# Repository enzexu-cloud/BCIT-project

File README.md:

# 💫 About Me:
Enze Xu (徐恩泽) is a highly adaptable and analytical Mechatronics & Robotics student at BCIT specializing in automation control and embedded systems. After two years of intensive study, he has gained hands-on experience in PLC programming, circuit design, and microcontroller development, he has built a strong foundation in real-time control and system integration. Skilled in embedded C/ Assembly, hardware/software design, and diagnostics, he excels at developing and troubleshooting automation equipment.<br><br>He is passionate about contributing his expertise in automation and embedded technology.

## 🌐 Socials:

# 💻 Tech Stack:
      
# 📊 GitHub Stats:
<br/>
<br/>

---

<!-- Proudly created with GPRM ( https://gprm.itsvg.in ) -->

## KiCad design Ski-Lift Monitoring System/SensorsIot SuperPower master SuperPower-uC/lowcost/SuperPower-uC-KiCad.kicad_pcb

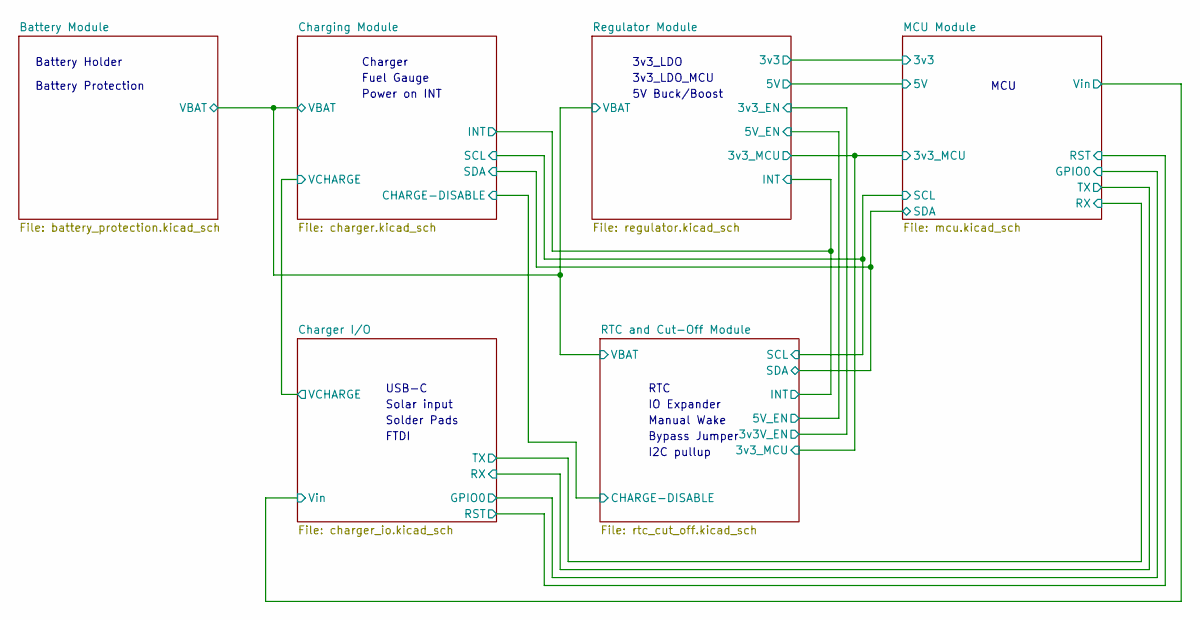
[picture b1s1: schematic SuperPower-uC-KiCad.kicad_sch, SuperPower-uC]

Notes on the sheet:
Battery Protection
Solar input
Bypass Jumper
3v3_LDO
3v3_LDO_MCU
RTC
Battery Holder
I2C pullup
5V Buck/Boost
MCU
FTDI
Fuel Gauge
Charger
Power on INT
IO Expander
USB-C
Manual Wake
Solder Pads

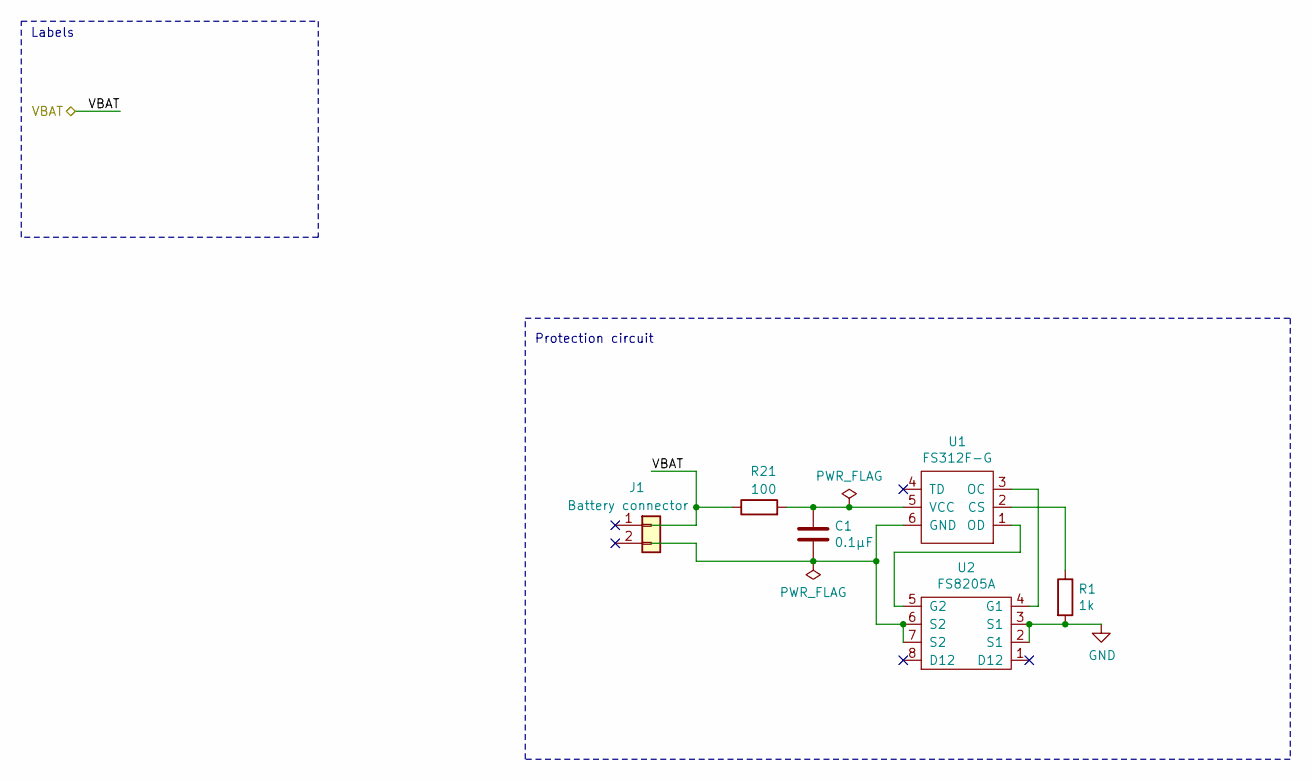
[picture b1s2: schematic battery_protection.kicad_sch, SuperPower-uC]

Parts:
C1: 0.1µF; C_0603_1608Metric_Pad1.08x0.95mm_HandSolder; LCSC C14858
J1: Battery connector; JST_EH_S2B-EH_1x02_P2.50mm_Horizontal; LCSC C157931
R1: 1k; R_0603_1608Metric_Pad0.98x0.95mm_HandSolder; LCSC C21190
R21: 100; R_0603_1608Metric_Pad0.98x0.95mm_HandSolder; LCSC C22775
U1: FS312F-G; SOT-23-6_Handsoldering; LCSC C82736
U2: FS8205A; TSSOP-8_4.4x3mm_P0.65mm; LCSC C16052

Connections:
/Battery Module/VBAT: J1.1, R21.1; also elsewhere on the board
GND: R1.2, U2.2 (S1), U2.3 (S1); also elsewhere on the board
unnamed: C1.1, R21.2, U1.5 (VCC)
unnamed: R1.1, U1.2 (CS)
unnamed: U1.1 (OD), U2.5 (G2)
unnamed: U1.3 (OC), U2.4 (G1)

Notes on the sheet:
Protection circuit
Labels

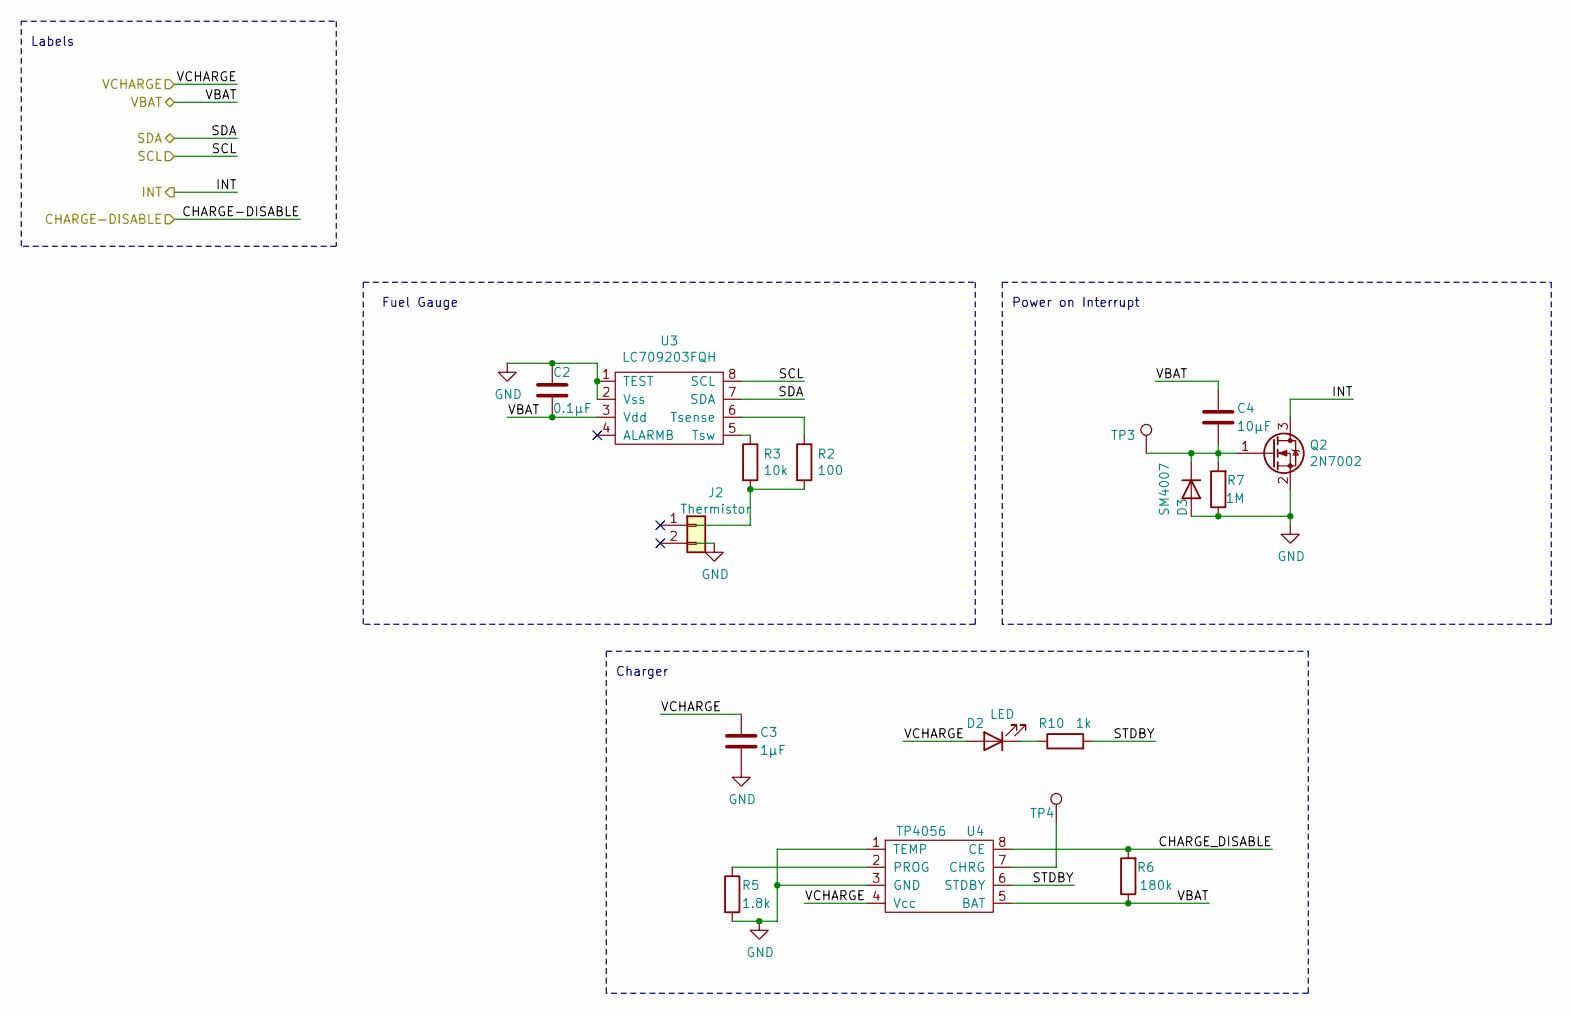
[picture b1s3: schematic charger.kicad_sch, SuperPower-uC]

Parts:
C2: 0.1µF; C_0603_1608Metric_Pad1.08x0.95mm_HandSolder; LCSC C14858
C3: 1µF; C_0603_1608Metric_Pad1.08x0.95mm_HandSolder; LCSC C15849
C4: 10µF; C_0603_1608Metric_Pad1.08x0.95mm_HandSolder; LCSC C19702
D2: LED; LED_0603_1608Metric_Pad1.05x0.95mm_HandSolder; LCSC C72041
D3: SM4007; D_MELF; LCSC C64898
J2: Thermistor; JST_EH_S2B-EH_1x02_P2.50mm_Horizontal; LCSC C76589
Q2: 2N7002; SOT-23; LCSC C8545
R2: 100; R_0603_1608Metric_Pad0.98x0.95mm_HandSolder; LCSC C22775
R3: 10k; R_0603_1608Metric_Pad0.98x0.95mm_HandSolder; LCSC C25804
R5: 1.8k; R_0603_1608Metric_Pad0.98x0.95mm_HandSolder; LCSC C4177
R6: 180k; R_0603_1608Metric_Pad0.98x0.95mm_HandSolder; LCSC C22827
R7: 1M; R_0603_1608Metric_Pad0.98x0.95mm_HandSolder; LCSC C22935
R10: 1k; R_0603_1608Metric_Pad0.98x0.95mm_HandSolder; LCSC C21190
TP3, TP4: TestPoint; TestPoint_Pad_1.5x1.5mm
U3: LC709203FQH; WDFN-8-1EP_4x3mm_P0.65mm_EP2.4x1.8mm; LCSC C152311
U4: TP4056; SOP-8_3.9x4.9mm_P1.27mm; LCSC C16581

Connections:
/Battery Module/VBAT: C2.2, C4.1, R6.1, U3.3 (Vdd), U4.5 (BAT); also elsewhere on the board
/Charger I/O/VCHARGE: C3.1, D2.2 (A), U4.4 (Vcc); also elsewhere on the board
/Charging Module/INT: Q2.3 (D); also elsewhere on the board
/Charging Module/SCL: U3.8 (SCL); also elsewhere on the board
/Charging Module/SDA: U3.7 (SDA); also elsewhere on the board
/Charging Module/STDBY: R10.2, U4.6 (STDBY)
CH_DIS: R6.2, U4.8 (CE); also elsewhere on the board
GND: C2.1, C3.2, D3.2 (A), J2.2, Q2.2 (S), R5.2, R7.1, U3.1 (TEST), U3.2 (Vss), U4.1 (TEMP), U4.3 (GND); also elsewhere on the board
unnamed: C4.2, D3.1 (K), Q2.1 (G), R7.2, TP3.1
unnamed: D2.1 (K), R10.1
unnamed: R2.1, U3.6 (Tsense)
unnamed: R3.1, U3.5 (Tsw)
unnamed: R5.1, U4.2 (PROG)
unnamed: TP4.1, U4.7 (CHRG)

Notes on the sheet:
Labels
Charger
Power on Interrupt
Fuel Gauge

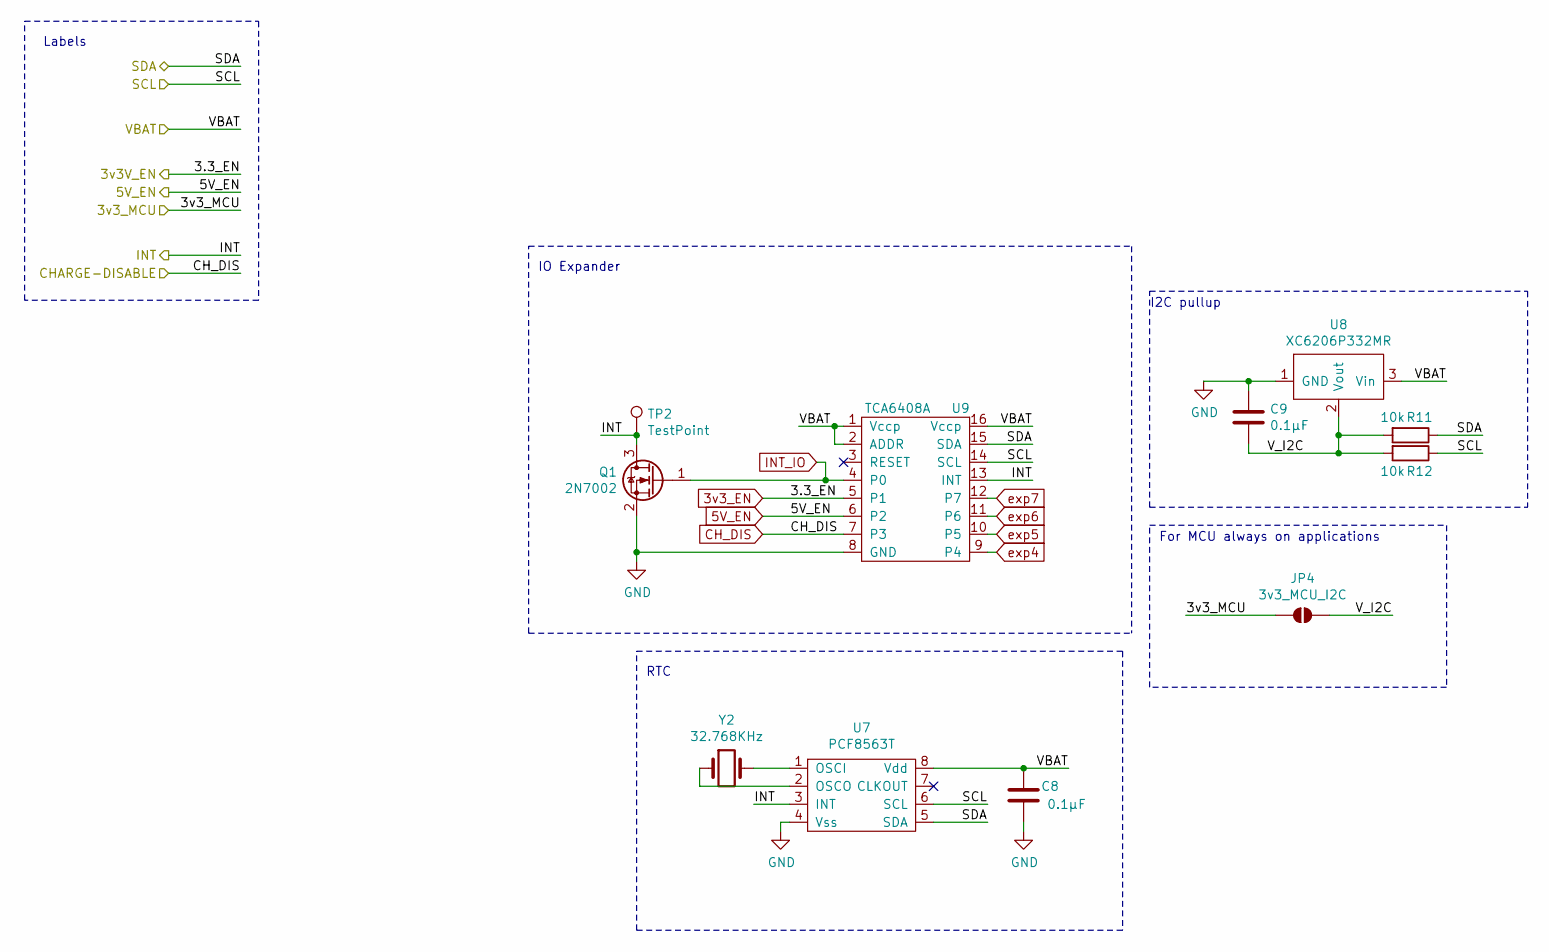
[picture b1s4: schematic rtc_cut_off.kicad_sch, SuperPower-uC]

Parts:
C8, C9: 0.1µF; C_0603_1608Metric_Pad1.08x0.95mm_HandSolder; LCSC C14858
JP4: 3v3_MCU_I2C; SolderJumper-2_P1.3mm_Open_Pad1.0x1.5mm
Q1: 2N7002; SOT-23; LCSC C8545
R11, R12: 10k; R_0603_1608Metric_Pad0.98x0.95mm_HandSolder; LCSC C25804
TP2: TestPoint; TestPoint_Pad_1.5x1.5mm
U7: PCF8563T; SOIC-8_3.9x4.9mm_P1.27mm; LCSC C7440
U8: XC6206P332MR; SOT-23_Handsoldering; LCSC C5446
U9: TCA6408A; TSSOP-16_4.4x5mm_P0.65mm; LCSC C206177
Y2: 32.768KHz; Crystal_SMD_3215-2Pin_3.2x1.5mm; LCSC C32346

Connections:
3v3_EN: U9.5 (P1); also elsewhere on the board
5V_EN: U9.6 (P2); also elsewhere on the board
/Battery Module/VBAT: C8.2, U7.8 (Vdd), U8.3 (Vin), U9.1 (Vccp), U9.2 (ADDR), U9.16 (Vccp); also elsewhere on the board
/Charging Module/INT: Q1.3 (D), TP2.1, U7.3 (INT), U9.13 (INT); also elsewhere on the board
/Charging Module/SCL: R12.1, U7.6 (SCL), U9.14 (SCL); also elsewhere on the board
/Charging Module/SDA: R11.1, U7.5 (SDA), U9.15 (SDA); also elsewhere on the board
/MCU Module/3v3_MCU: JP4.1 (A); also elsewhere on the board
/RTC and Cut-Off Module/V_I2C: C9.2, JP4.2 (B), R11.2, R12.2, U8.2 (Vout)
CH_DIS: U9.7 (P3); also elsewhere on the board
GND: C8.1, C9.1, Q1.2 (S), U7.4 (Vss), U8.1 (GND), U9.8 (GND); also elsewhere on the board
INT_IO: Q1.1 (G), U9.4 (P0); also elsewhere on the board
unnamed: U7.1 (OSCI), Y2.2
unnamed: U7.2 (OSCO), Y2.1
exp4: U9.9 (P4); also elsewhere on the board
exp5: U9.10 (P5); also elsewhere on the board
exp6: U9.11 (P6); also elsewhere on the board
exp7: U9.12 (P7); also elsewhere on the board

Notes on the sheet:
For MCU always on applications
I2C pullup
Labels
IO Expander
RTC

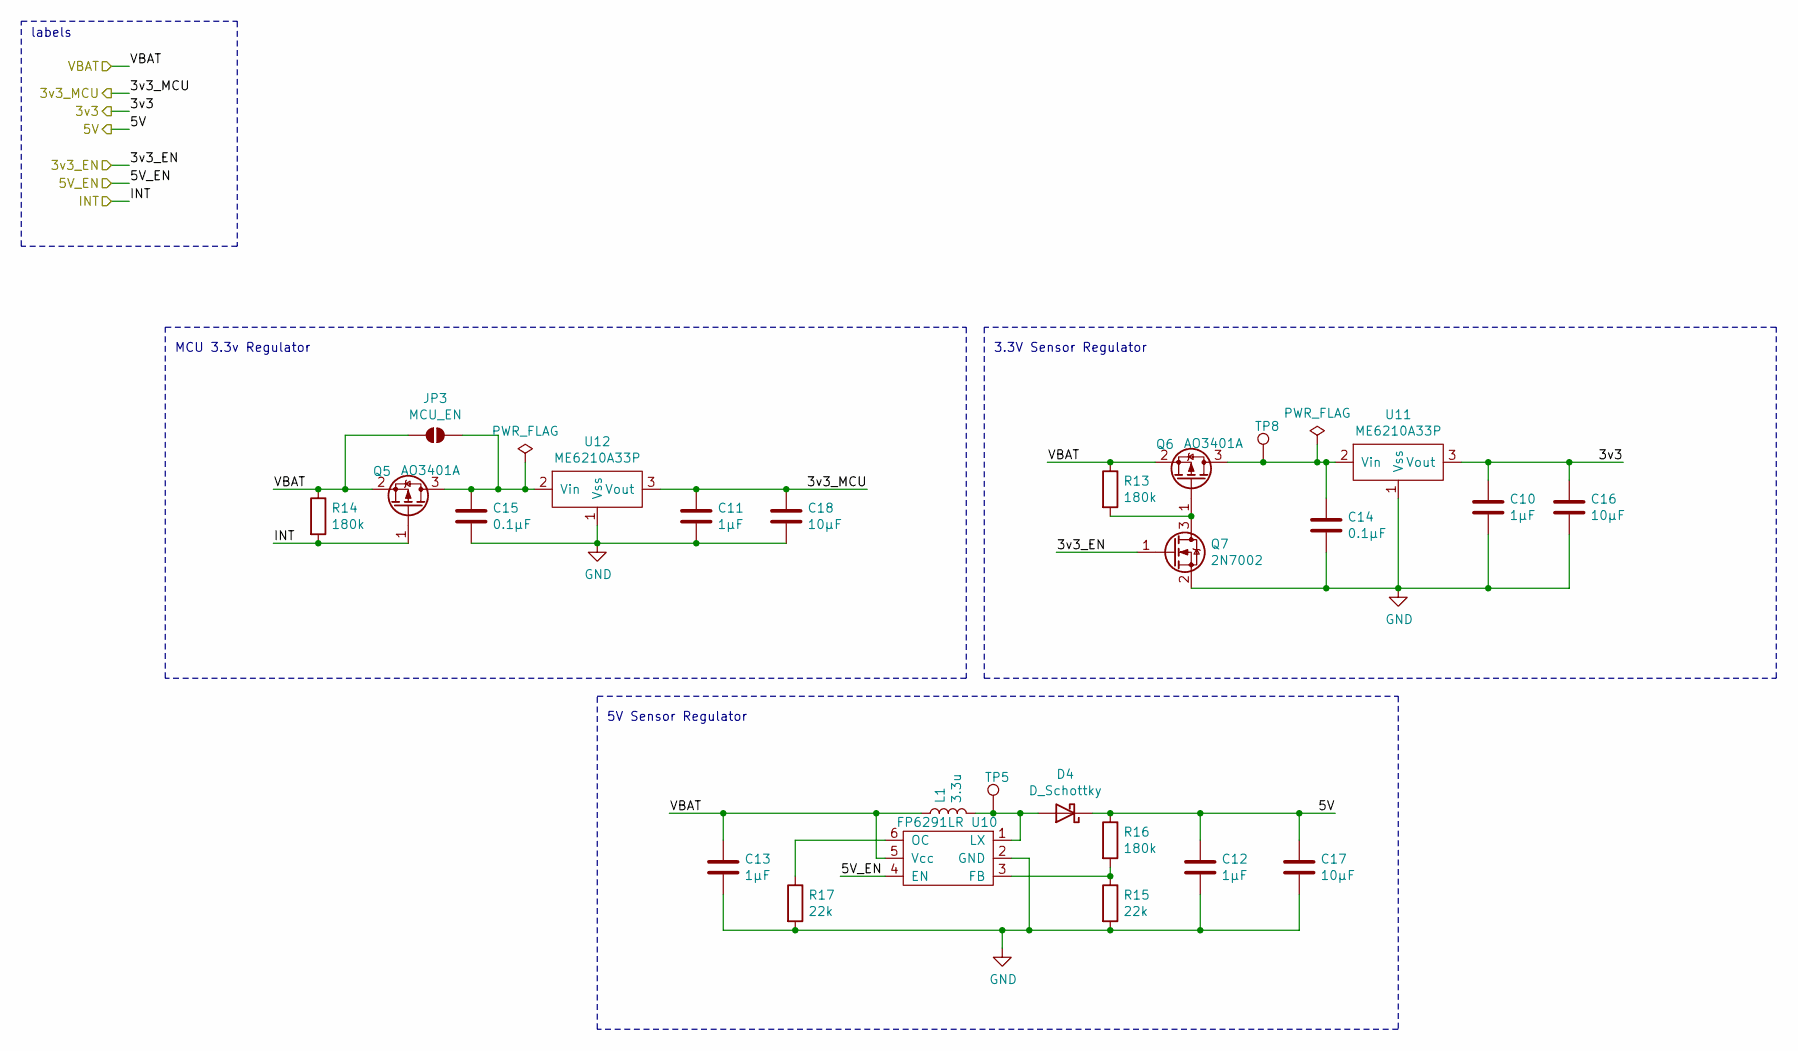
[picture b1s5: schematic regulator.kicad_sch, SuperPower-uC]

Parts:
C10, C11, C12, C13: 1µF; C_0603_1608Metric_Pad1.08x0.95mm_HandSolder; LCSC C15849
C14, C15: 0.1µF; C_0603_1608Metric_Pad1.08x0.95mm_HandSolder; LCSC C14858
C16, C17, C18: 10µF; C_0603_1608Metric_Pad1.08x0.95mm_HandSolder; LCSC C19702
D4: D_Schottky; D_SOD-123; LCSC C8598
JP3: MCU_EN; SolderJumper-2_P1.3mm_Open_Pad1.0x1.5mm
L1: 3.3u; L_Bourns_SRP7028A_7.3x6.6mm; LCSC C280586
Q5, Q6: AO3401A; SOT-23_Handsoldering; LCSC C347476
Q7: 2N7002; SOT-23; LCSC C8545
R13, R14, R16: 180k; R_0603_1608Metric_Pad0.98x0.95mm_HandSolder; LCSC C22827
R15, R17: 22k; R_0603_1608Metric_Pad0.98x0.95mm_HandSolder; LCSC C17560
TP5, TP8: TestPoint; TestPoint_Pad_1.5x1.5mm
U10: FP6291LR; SOT-23-6_Handsoldering; LCSC C18701
U11, U12: ME6210A33P; SOT-89-3_Handsoldering; LCSC C85233

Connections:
3v3_EN: Q7.1 (G); also elsewhere on the board
5V_EN: U10.4 (EN); also elsewhere on the board
/Battery Module/VBAT: C13.1, JP3.1 (A), L1.1, Q5.2 (S), Q6.2 (S), R13.1, R14.1, U10.5 (Vcc); also elsewhere on the board
/Charging Module/INT: Q5.1 (G), R14.2; also elsewhere on the board
/MCU Module/3v3: C10.1, C16.1, U11.3 (Vout); also elsewhere on the board
/MCU Module/3v3_MCU: C11.1, C18.1, U12.3 (Vout); also elsewhere on the board
/MCU Module/5V: C12.1, C17.1, D4.1 (K), R16.1; also elsewhere on the board
GND: C10.2, C11.2, C12.2, C13.2, C14.2, C15.2, C16.2, C17.2, C18.2, Q7.2 (S), R15.2, R17.2, U10.2 (GND), U11.1 (Vss), U12.1 (Vss); also elsewhere on the board
unnamed: C14.1, Q6.3 (D), TP8.1, U11.2 (Vin)
unnamed: C15.1, JP3.2 (B), Q5.3 (D), U12.2 (Vin)
unnamed: D4.2 (A), L1.2, TP5.1, U10.1 (LX)
unnamed: Q6.1 (G), Q7.3 (D), R13.2
unnamed: R15.1, R16.2, U10.3 (FB)
unnamed: R17.1, U10.6 (OC)

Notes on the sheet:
MCU 3.3v Regulator
3.3V Sensor Regulator
labels
5V Sensor Regulator

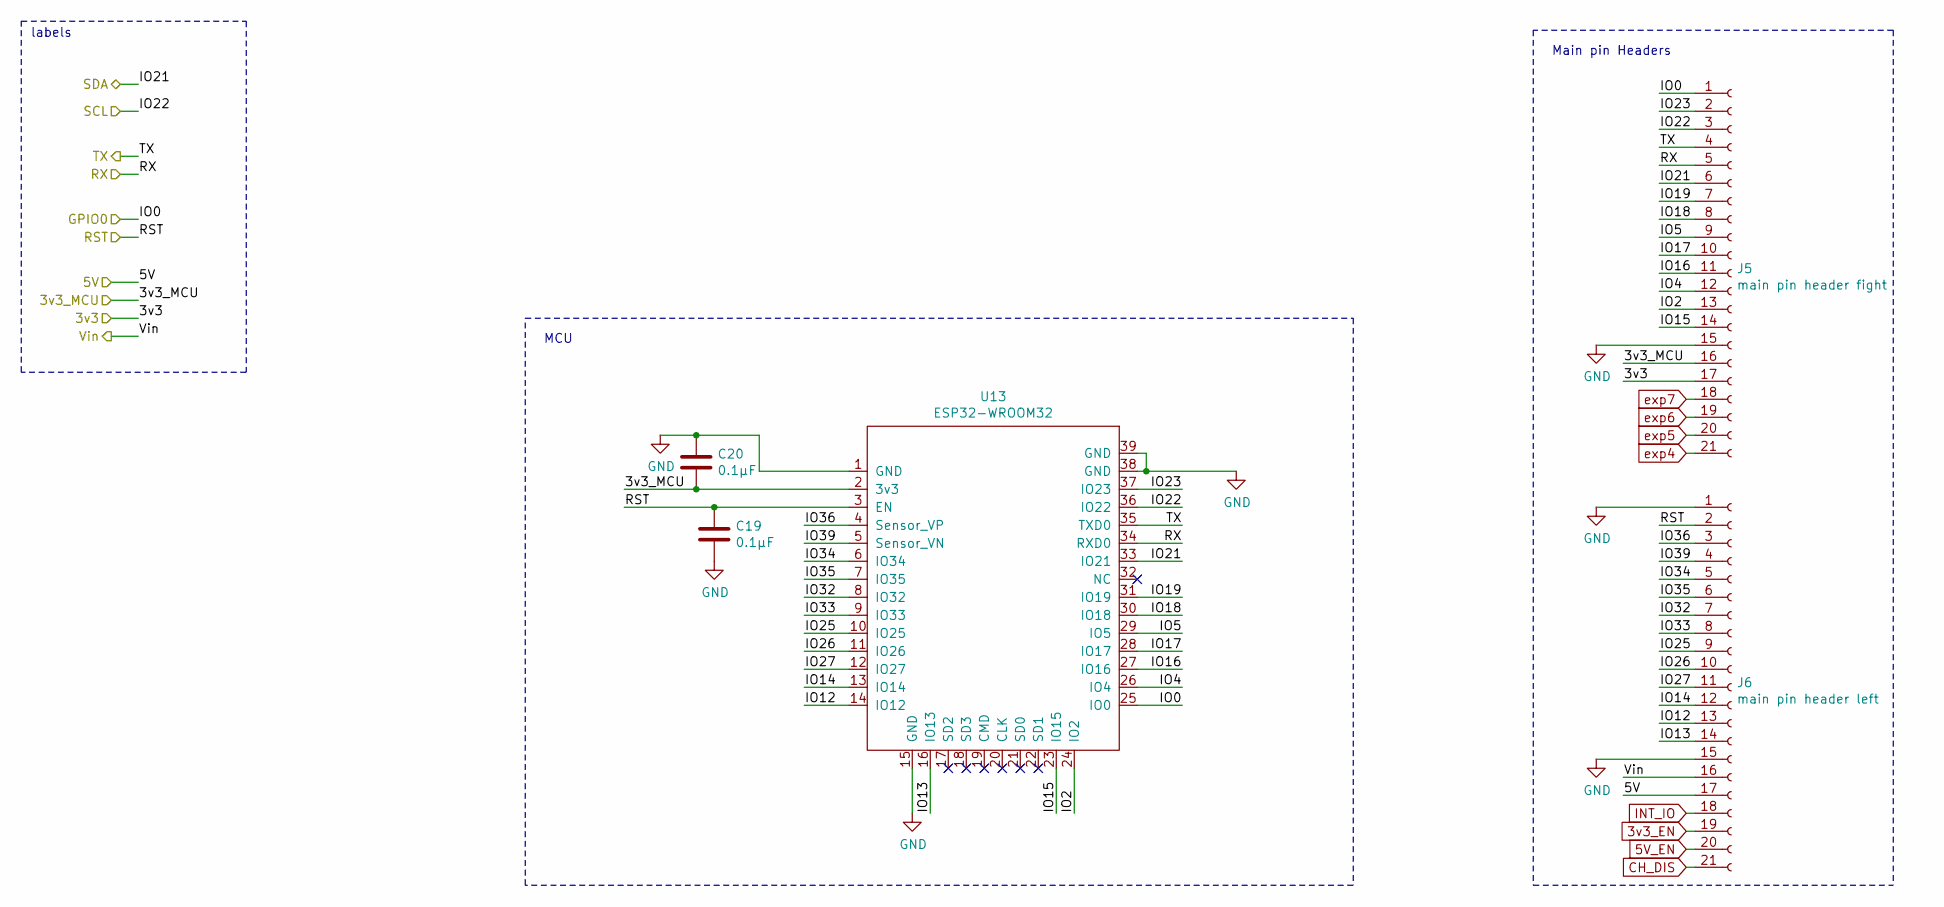
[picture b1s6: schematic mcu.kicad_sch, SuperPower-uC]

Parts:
C19, C20: 0.1µF; C_0603_1608Metric_Pad1.08x0.95mm_HandSolder; LCSC C14858
J5: main pin header fight; PinSocket_1x21_P2.54mm_Vertical
J6: main pin header left; PinSocket_1x21_P2.54mm_Vertical
U13: ESP32-WROOM32; ESP32-WROOM-32; LCSC C82899

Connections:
3v3_EN: J6.19; also elsewhere on the board
5V_EN: J6.20; also elsewhere on the board
/Charger I/O/GPIO0: J5.1, U13.25 (IO0); also elsewhere on the board
/Charger I/O/RST: C19.1, J6.2, U13.3 (EN); also elsewhere on the board
/Charger I/O/RX: J5.4, U13.35 (TXD0); also elsewhere on the board
/Charger I/O/VCHARGE: J6.16; also elsewhere on the board
/Charging Module/SCL: J5.3, U13.36 (IO22); also elsewhere on the board
/Charging Module/SDA: J5.6, U13.33 (IO21); also elsewhere on the board
/MCU Module/3v3: J5.17; also elsewhere on the board
/MCU Module/3v3_MCU: C20.2, J5.16, U13.2 (3v3); also elsewhere on the board
/MCU Module/5V: J6.17; also elsewhere on the board
/MCU Module/IO2: J5.13, U13.24 (IO2)
/MCU Module/IO4: J5.12, U13.26 (IO4)
/MCU Module/IO5: J5.9, U13.29 (IO5)
/MCU Module/IO12: J6.13, U13.14 (IO12)
/MCU Module/IO13: J6.14, U13.16 (IO13)
/MCU Module/IO14: J6.12, U13.13 (IO14)
/MCU Module/IO15: J5.14, U13.23 (IO15)
/MCU Module/IO16: J5.11, U13.27 (IO16)
/MCU Module/IO17: J5.10, U13.28 (IO17)
/MCU Module/IO18: J5.8, U13.30 (IO18)
/MCU Module/IO19: J5.7, U13.31 (IO19)
/MCU Module/IO23: J5.2, U13.37 (IO23)
/MCU Module/IO25: J6.9, U13.10 (IO25)
/MCU Module/IO26: J6.10, U13.11 (IO26)
/MCU Module/IO27: J6.11, U13.12 (IO27)
/MCU Module/IO32: J6.7, U13.8 (IO32)
/MCU Module/IO33: J6.8, U13.9 (IO33)
/MCU Module/IO34: J6.5, U13.6 (IO34)
/MCU Module/IO35: J6.6, U13.7 (IO35)
/MCU Module/IO36: J6.3, U13.4 (Sensor_VP)
/MCU Module/IO39: J6.4, U13.5 (Sensor_VN)
/MCU Module/RX: J5.5, U13.34 (RXD0); also elsewhere on the board
CH_DIS: J6.21; also elsewhere on the board
GND: C19.2, C20.1, J5.15, J6.1, J6.15, U13.1 (GND), U13.15 (GND), U13.38 (GND), U13.39 (GND); also elsewhere on the board
INT_IO: J6.18; also elsewhere on the board
exp4: J5.21; also elsewhere on the board
exp5: J5.20; also elsewhere on the board
exp6: J5.19; also elsewhere on the board
exp7: J5.18; also elsewhere on the board

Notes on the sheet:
labels
MCU
Main pin Headers

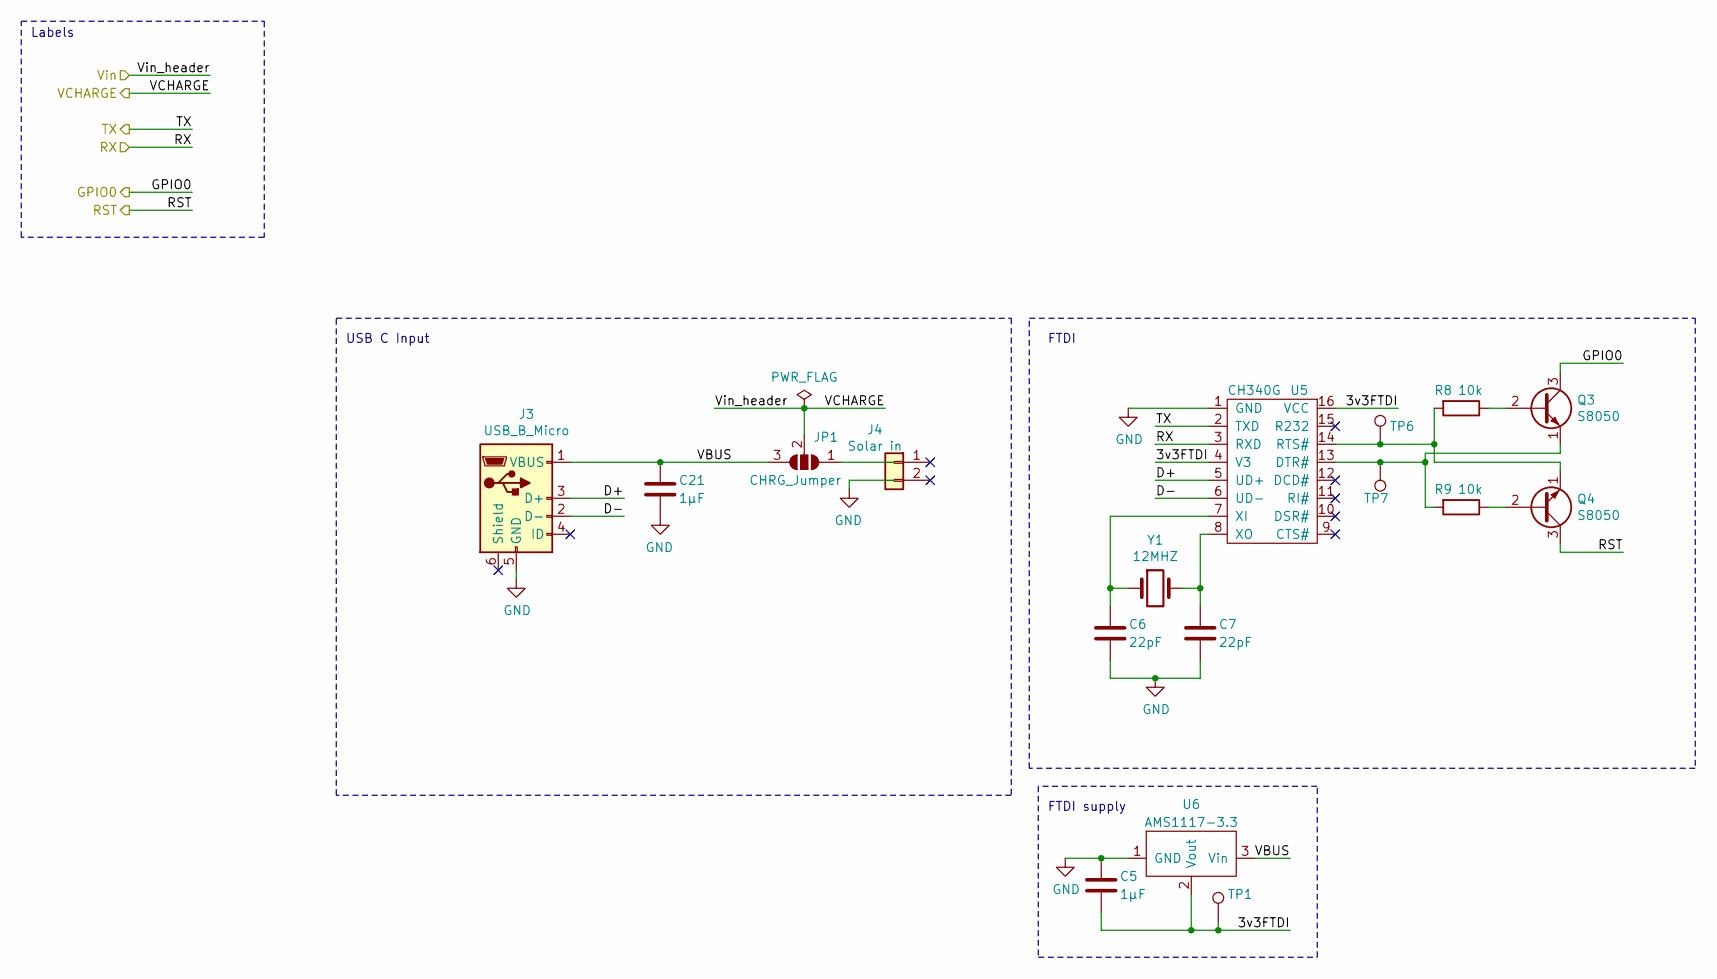
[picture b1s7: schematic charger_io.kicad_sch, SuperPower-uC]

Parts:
C5, C21: 1µF; C_0603_1608Metric_Pad1.08x0.95mm_HandSolder; LCSC C15849
C6: 22pF; R_0603_1608Metric_Pad0.98x0.95mm_HandSolder; LCSC C1653
C7: 22pF; C_0603_1608Metric_Pad1.08x0.95mm_HandSolder; LCSC C1653
J3: USB_B_Micro; USB_Micro-B_Molex-105017-0001; LCSC C319164
J4: Solar in; JST_EH_S2B-EH_1x02_P2.50mm_Horizontal; LCSC C157931
JP1: CHRG_Jumper; SolderJumper-3_P1.3mm_Open_Pad1.0x1.5mm
Q3, Q4: S8050; SOT-23_Handsoldering; LCSC C111272
R8, R9: 10k; R_0603_1608Metric_Pad0.98x0.95mm_HandSolder; LCSC C25804
TP1, TP6, TP7: TestPoint; TestPoint_Pad_1.5x1.5mm
U5: CH340G; SOP-16_4.55x10.3mm_P1.27mm; LCSC C14267
U6: AMS1117-3.3; SOT-223-3_TabPin2; LCSC C6186
Y1: 12MHZ; Crystal_SMD_3225-4Pin_3.2x2.5mm_HandSoldering; LCSC C9002

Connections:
/Charger I/O/3v3FTDI: C5.2, TP1.1, U5.4 (V3), U5.16 (VCC), U6.2 (Vout)
/Charger I/O/D+: J3.3 (D+), U5.5 (UD+)
/Charger I/O/D-: J3.2 (D-), U5.6 (UD-)
/Charger I/O/GPIO0: Q3.3 (C); also elsewhere on the board
/Charger I/O/RST: Q4.3 (C); also elsewhere on the board
/Charger I/O/RX: U5.3 (RXD); also elsewhere on the board
/Charger I/O/VBUS: C21.1, J3.1 (VBUS), JP1.3 (B), U6.3 (Vin)
/Charger I/O/VCHARGE: JP1.2 (C); also elsewhere on the board
/MCU Module/RX: U5.2 (TXD); also elsewhere on the board
GND: C5.1, C6.2, C7.2, C21.2, J3.5 (GND), J4.2, U5.1 (GND), U6.1 (GND); also elsewhere on the board
unnamed: C6.1, U5.7 (XI), Y1.1
unnamed: C7.1, U5.8 (XO), Y1.2
unnamed: J4.1, JP1.1 (A)
unnamed: Q3.1 (E), R9.2, TP7.1, U5.13 (DTR#)
unnamed: Q3.2 (B), R8.1
unnamed: Q4.1 (E), R8.2, TP6.1, U5.14 (RTS#)
unnamed: Q4.2 (B), R9.1

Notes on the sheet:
FTDI supply
USB C Input
Labels
FTDI

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
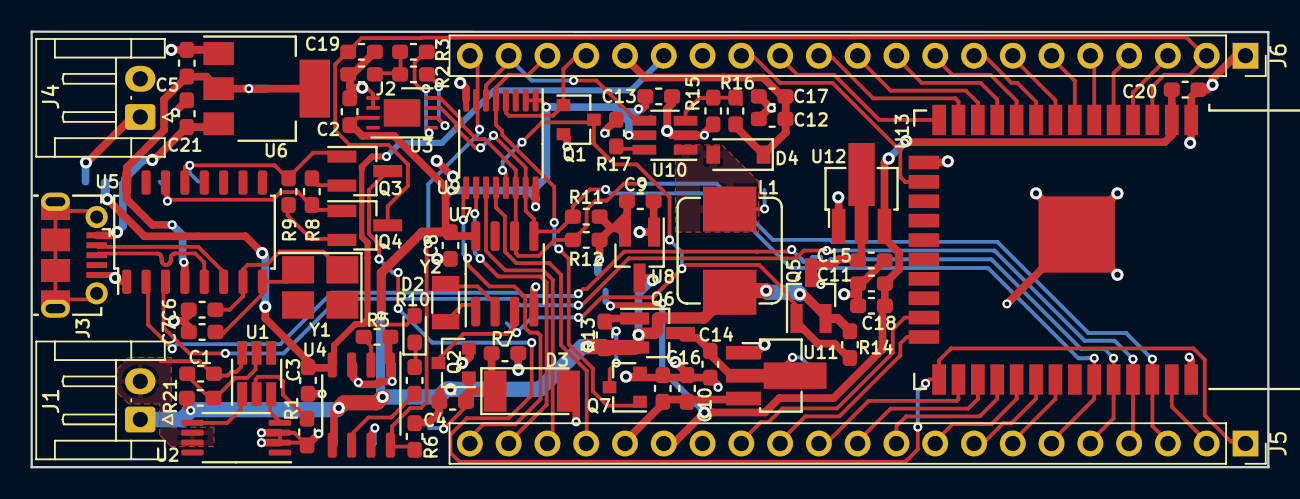
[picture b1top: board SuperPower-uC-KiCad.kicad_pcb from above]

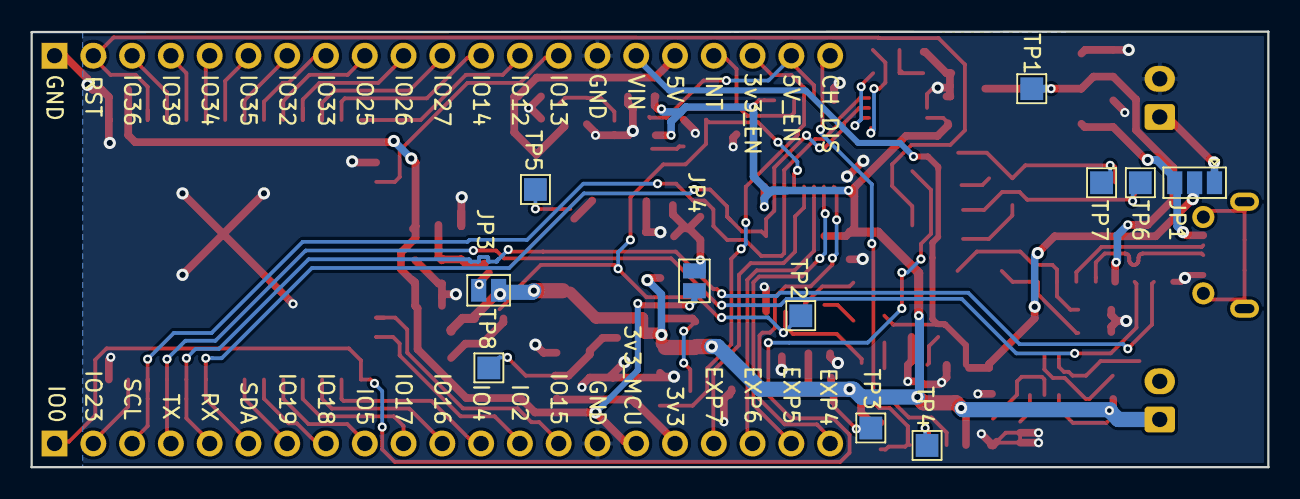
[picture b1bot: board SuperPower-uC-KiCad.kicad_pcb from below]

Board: 2 copper layers, 81.0 x 28.5 mm, 81 parts (11 on the bottom side), 75 nets.

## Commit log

2025-01-16 Create MSP430 PWM Control Code
2025-01-16 Create MSP430 Software Encoder Code
2025-01-16 Create MSP430 Keypad PWM Control Code
2025-01-20 Upload electrical labs
2025-01-20 Upload MSP430 projects from ROBT 3356 Controller System
2025-01-21 Updated folder name
2025-01-21 Created images folder
2025-05-19 Upload Ski-Lift project
2025-05-19 Upload PCB design
2025-05-19 Upload SuperPower BOM
2025-05-19 Upload project budget plan
2025-05-19 Upload poster
2025-05-21 Upload PLC Elevator Project
2025-05-21 Upload pdf report

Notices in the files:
Ski-Lift Monitoring System/SensorsIot SuperPower master SuperPower-uC/lowcost/SuperPower-uC-KiCad.kicad_sch:
Licence: CERN-OHL-W
